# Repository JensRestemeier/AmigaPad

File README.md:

# AmigaPad
This is a copy of the schematic for the CD32 joypad from https://www.mrdictionary.net/PSCD32/diary/sites/CD32Gamepad_gerdkautzmann_de.html in KiCad, which is based on reverse engineered hardware.
I made a small PCB, which is mostly for testing and development work. So far I had no time to make a case for it.

I don't know what kind of Ferrite Bead the original Joypad uses, so I just put in a bridge. There is a choice of populating vertical buttons for the shoulder buttons, or plain horizontal buttons on the component side. The button
above the start button has no function in a normal Amiga software.

Classic Amiga software will see the directions, "red" as fire and "blue" as PotY.

CD32-compatible software will see the directions, four face buttons, two shoulder buttons and a start button.

You can preview the KiCad project on [KiCanvas](https://kicanvas.org/?repo=https%3A%2F%2Fgithub.com%2FJensRestemeier%2FAmigaPad%2Ftree%2Fmain%2FKiCad).

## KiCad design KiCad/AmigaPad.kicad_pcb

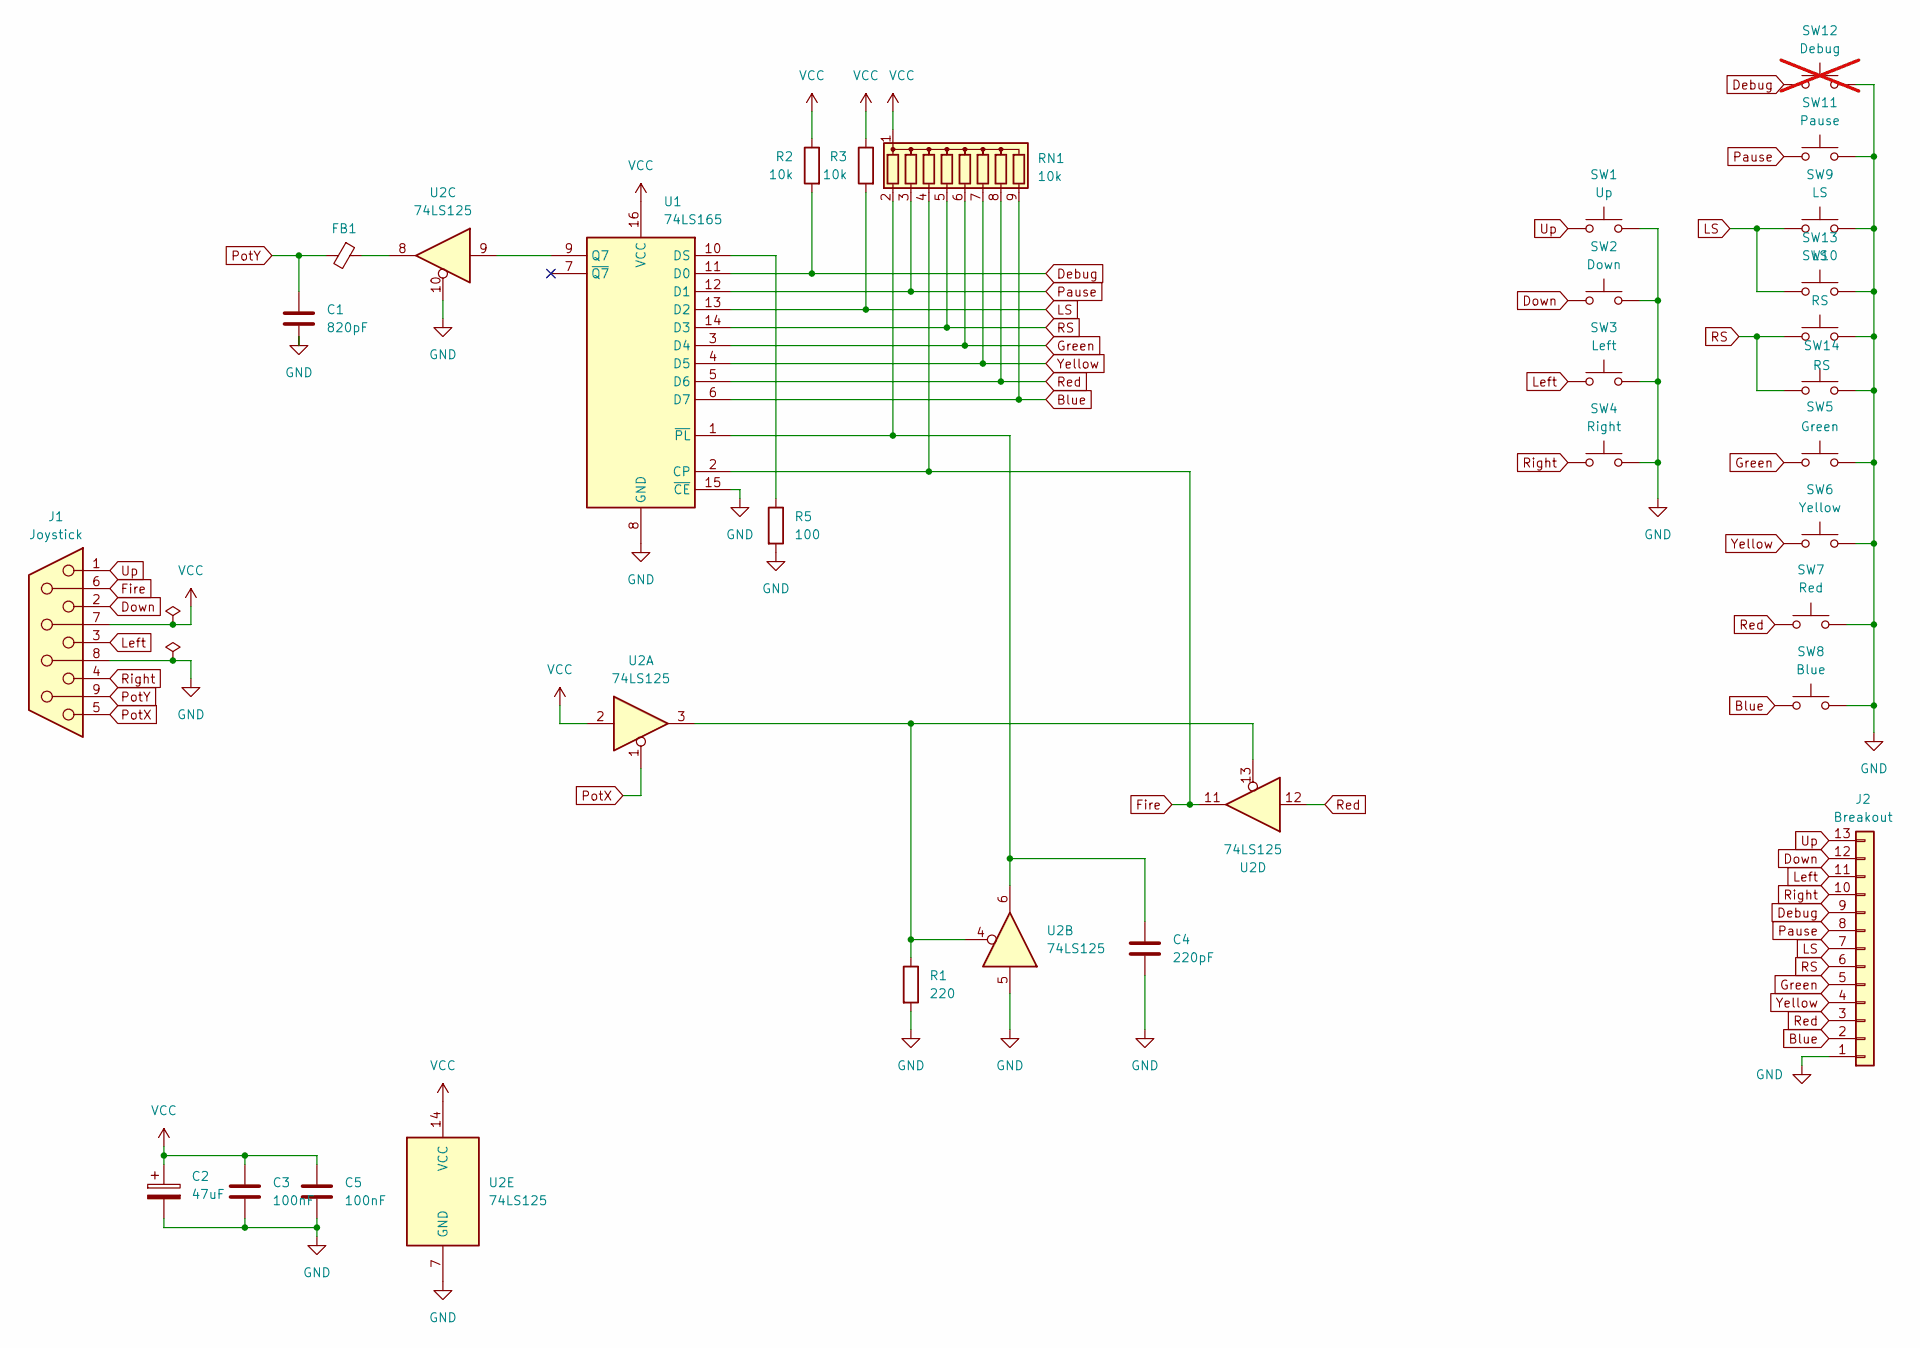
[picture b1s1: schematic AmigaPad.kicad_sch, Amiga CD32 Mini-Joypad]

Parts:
C1: 820pF; C_Disc_D4.3mm_W1.9mm_P5.00mm
C2: 47uF; CP_Radial_D5.0mm_P2.50mm
C3, C5: 100nF; C_Disc_D4.3mm_W1.9mm_P5.00mm
C4: 220pF; C_Disc_D4.3mm_W1.9mm_P5.00mm
FB1: FerriteBead_Small; L_Axial_L5.3mm_D2.2mm_P10.16mm_Horizontal_Vishay_IM-1
J1: Joystick; DSUB-9_Socket_EdgeMount_P2.77mm
J2: Breakout; PinHeader_1x13_P2.54mm_Vertical
R1: 220; R_Axial_DIN0207_L6.3mm_D2.5mm_P10.16mm_Horizontal
R2, R3: 10k; R_Axial_DIN0207_L6.3mm_D2.5mm_P10.16mm_Horizontal
R5: 100; R_Axial_DIN0207_L6.3mm_D2.5mm_P10.16mm_Horizontal
RN1: 10k; R_Array_SIP9
SW1: Up; SW_PUSH_6mm_H5mm
SW2: Down; SW_PUSH_6mm_H5mm
SW3: Left; SW_PUSH_6mm_H5mm
SW4: Right; SW_PUSH_6mm_H5mm
SW5: Green; SW_PUSH_6mm_H5mm
SW6: Yellow; SW_PUSH_6mm_H5mm
SW7: Red; SW_PUSH_6mm_H5mm
SW8: Blue; SW_PUSH_6mm_H5mm
SW9: LS; SW_PUSH_6mm_H5mm
SW10: RS; SW_PUSH_6mm_H5mm
SW11: Pause; SW_PUSH_6mm_H5mm
SW12: Debug; SW_PUSH_6mm_H5mm; not fitted
SW13: LS; SW_Tactile_SPST_Angled_PTS645Vx39-2LFS
SW14: RS; SW_Tactile_SPST_Angled_PTS645Vx39-2LFS
U1: 74LS165; DIP-16_W7.62mm
U2: 74LS125; DIP-14_W7.62mm

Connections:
Blue: J2.2, RN1.9 (R8), SW8.1, U1.6 (D7)
Debug: J2.9, R2.2, SW12.1, U1.11 (D0)
Down: J1.2, J2.12, SW2.1
Fire: J1.6, RN1.4 (R3), U1.2 (CP), U2.11
GND: C1.2, C2.2, C3.2, C4.2, C5.2, J1.8, J2.1, R1.2, R5.2, SW1.2, SW2.2, SW3.2, SW4.2, SW5.2, SW6.2, SW7.2, SW8.2, SW9.2, SW10.2, SW11.2, SW12.2, SW13.2, SW14.2, U1.8 (GND), U1.15 (~CE), U2.5, U2.7 (GND), U2.10
Green: J2.5, RN1.6 (R5), SW5.1, U1.3 (D4)
LS: J2.7, R3.2, SW9.1, SW13.1, U1.13 (D2)
Left: J1.3, J2.11, SW3.1
unnamed: FB1.1, U2.8
unnamed: R1.1, U2.3, U2.4, U2.13
unnamed: C4.1, RN1.2 (R1), U1.1 (~PL), U2.6
unnamed: R5.1, U1.10 (DS)
unnamed: U1.9 (Q7), U2.9
Pause: J2.8, RN1.3 (R2), SW11.1, U1.12 (D1)
PotX: J1.5, U2.1
PotY: C1.1, FB1.2, J1.9
RS: J2.6, RN1.5 (R4), SW10.1, SW14.1, U1.14 (D3)
Red: J2.3, RN1.8 (R7), SW7.1, U1.5 (D6), U2.12
Right: J1.4, J2.10, SW4.1
Up: J1.1, J2.13, SW1.1
VCC: C2.1, C3.1, C5.1, J1.7, R2.1, R3.1, RN1.1 (common), U1.16 (VCC), U2.2, U2.14 (VCC)
Yellow: J2.4, RN1.7 (R6), SW6.1, U1.4 (D5)

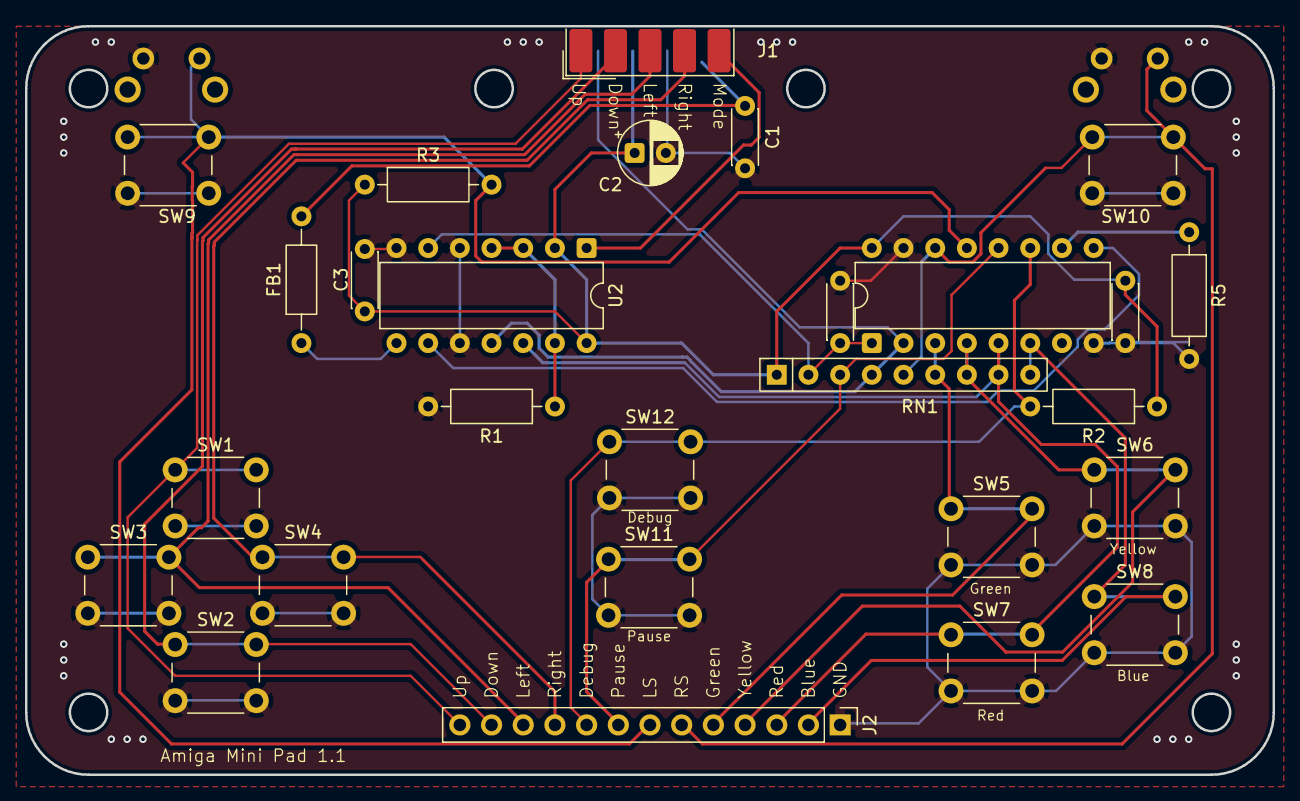
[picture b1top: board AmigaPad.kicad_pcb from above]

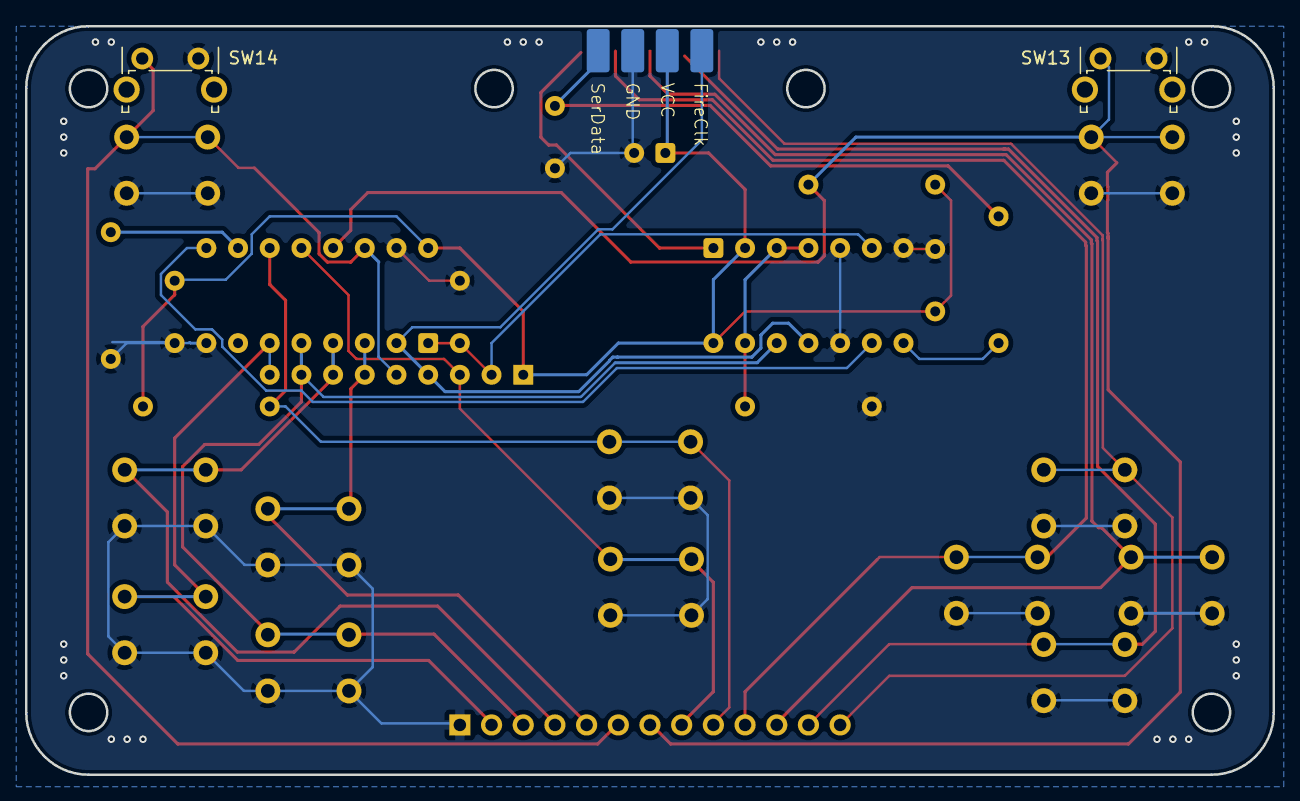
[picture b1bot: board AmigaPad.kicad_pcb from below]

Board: 2 copper layers, 100.0 x 60.0 mm, 29 parts (2 on the bottom side), 22 nets.

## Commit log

2026-05-19 initial import
